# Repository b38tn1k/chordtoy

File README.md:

# chordtoy

not an arpeggiator :-P

A dual channel MIDI chord generator with 'strumming' on one channel

I am not that great at building cases, here are my v1 and v2 prototypes.

[videos are easier than reading](https://www.youtube.com/playlist?list=PLZttbibA79ov0Y0J_pEOQnuLViuv8ho1e)

[how to install arduino midi library](https://github.com/FortySevenEffects/arduino_midi_library)

***built on a tested with MIDI Library version 4.3.1***

I wanted to play chords using the Arturia BeatStep Pro sequencer. This sits in the MIDI chain between the sequencer and the synth and uses the incoming MIDI note to stack a chord.*

## Features

- **Major / Minor Switch**. Major mode has a dominant 7th rather than major 7th chord, I haven't used it much.

- **Key Selector Pot:** Choose the key, other chords are mapped to scale for diatonic chords (I hope/think)

- **Chord Selector Pot:** Starting with the root note, add more notes to create a more complex sound. I tried to group the less complex sounds at low values and the more extreme sounds at high values. So, in Minor mode you can turn up to go from one note to a power chord to a minor chord to a minor 7, 9th, 11th, 13th.. with a couple more variations.

- **Inversion Mode Pot:** at zero the root note is at the bottom. At 100% the root note is at the top of the chord. Variations exist in between.

- **Strum Rate Pot:** When I first made this I just wanted to play simple block chords for techno-y sounding stabs on the DX. By accident I realized that the strummed chord can sound really nice and give some movement to a beat. Rhythms like [Legowelt](https://youtu.be/TGCxBVu1-sE) or [Flying Lotus](https://youtu.be/Pc0OaUQJtd4)... so at one extreme the chord plays all at once. At the other extreme the notes are plucked out one at a time slowly. Yes, like an arpeggiator. but no repeating or syncing cause I have a BeatStep that can keep time and play arpeggios :-)

- a **Legato Switch** changes the way MIDI noteoff messages are sent, allowing the strummed chord to ring out from a trigger or be cut short.

- a **Bypass Switch**, turn off the effect. More useful than turning everything down as in V1.

- a **Second MIDI Channel**. The ```MIDI_STRUM_CHANNEL``` does the 'strumming' chord effect. The ```MIDI_BLOCK_CHORD_CHANNEL``` is used to transmit block chords with the same notes as the Master chord, but with its own unique settings. It works nicely with my (newish) Behringer Crave in arp mode, giving me a 'free time' chord flourish from the DX and accompanying in time Arpeggios from the Crave. If you dont want the second channel stuff just don't let any devices listen on that channel and it should be fine, maybe tie the 'chord size' analog pin to ground :)

- **Second Inversion Mode**: as above but for the ```MIDI_BLOCK_CHORD_CHANNEL```, and with notes shifted 2 octaves cause I like it more.

- **Chord Size**: increase the number of notes in the ```MIDI_BLOCK_CHORD_CHANNEL``` by adding octaves above and below.

## Building

See below for my early prototypes, there is an ***in development*** kicad project included in this repo. Maybe someone good at EE can help? hmu!

Basically, you want to connect MIDI DINs to the Tx and Rx of the Arduino [I used this instructable](https://www.instructables.com/Send-and-Receive-MIDI-with-Arduino/). There are 6 pots, 3 switches and 2 LEDS in the current prototype, you can see the pin assignments in the .ino file.

Version 1 GPIOs per the .ino sketch:

Version 2 is similar with pot and switch IOs listed at top of the .ino file.

Prototype using a Pro Trinket (same pinouts as UNO) before I made it diatonic:

## Almost TODOs, Maybe just ideas

- MIDI CC Control for the various pots and switches
- Does [FortySevenEffect](https://github.com/FortySevenEffects/arduino_midi_library) MIDI library support transport, tempo, etc pass through?

\* Akai and Oberheim used to make boxes that did this sort of thing and this functionality is now built into heaps of DAWs, possible some synths. my Yamaha DX doesn't

Thank you to David Fodel for testing, advice and motivation!

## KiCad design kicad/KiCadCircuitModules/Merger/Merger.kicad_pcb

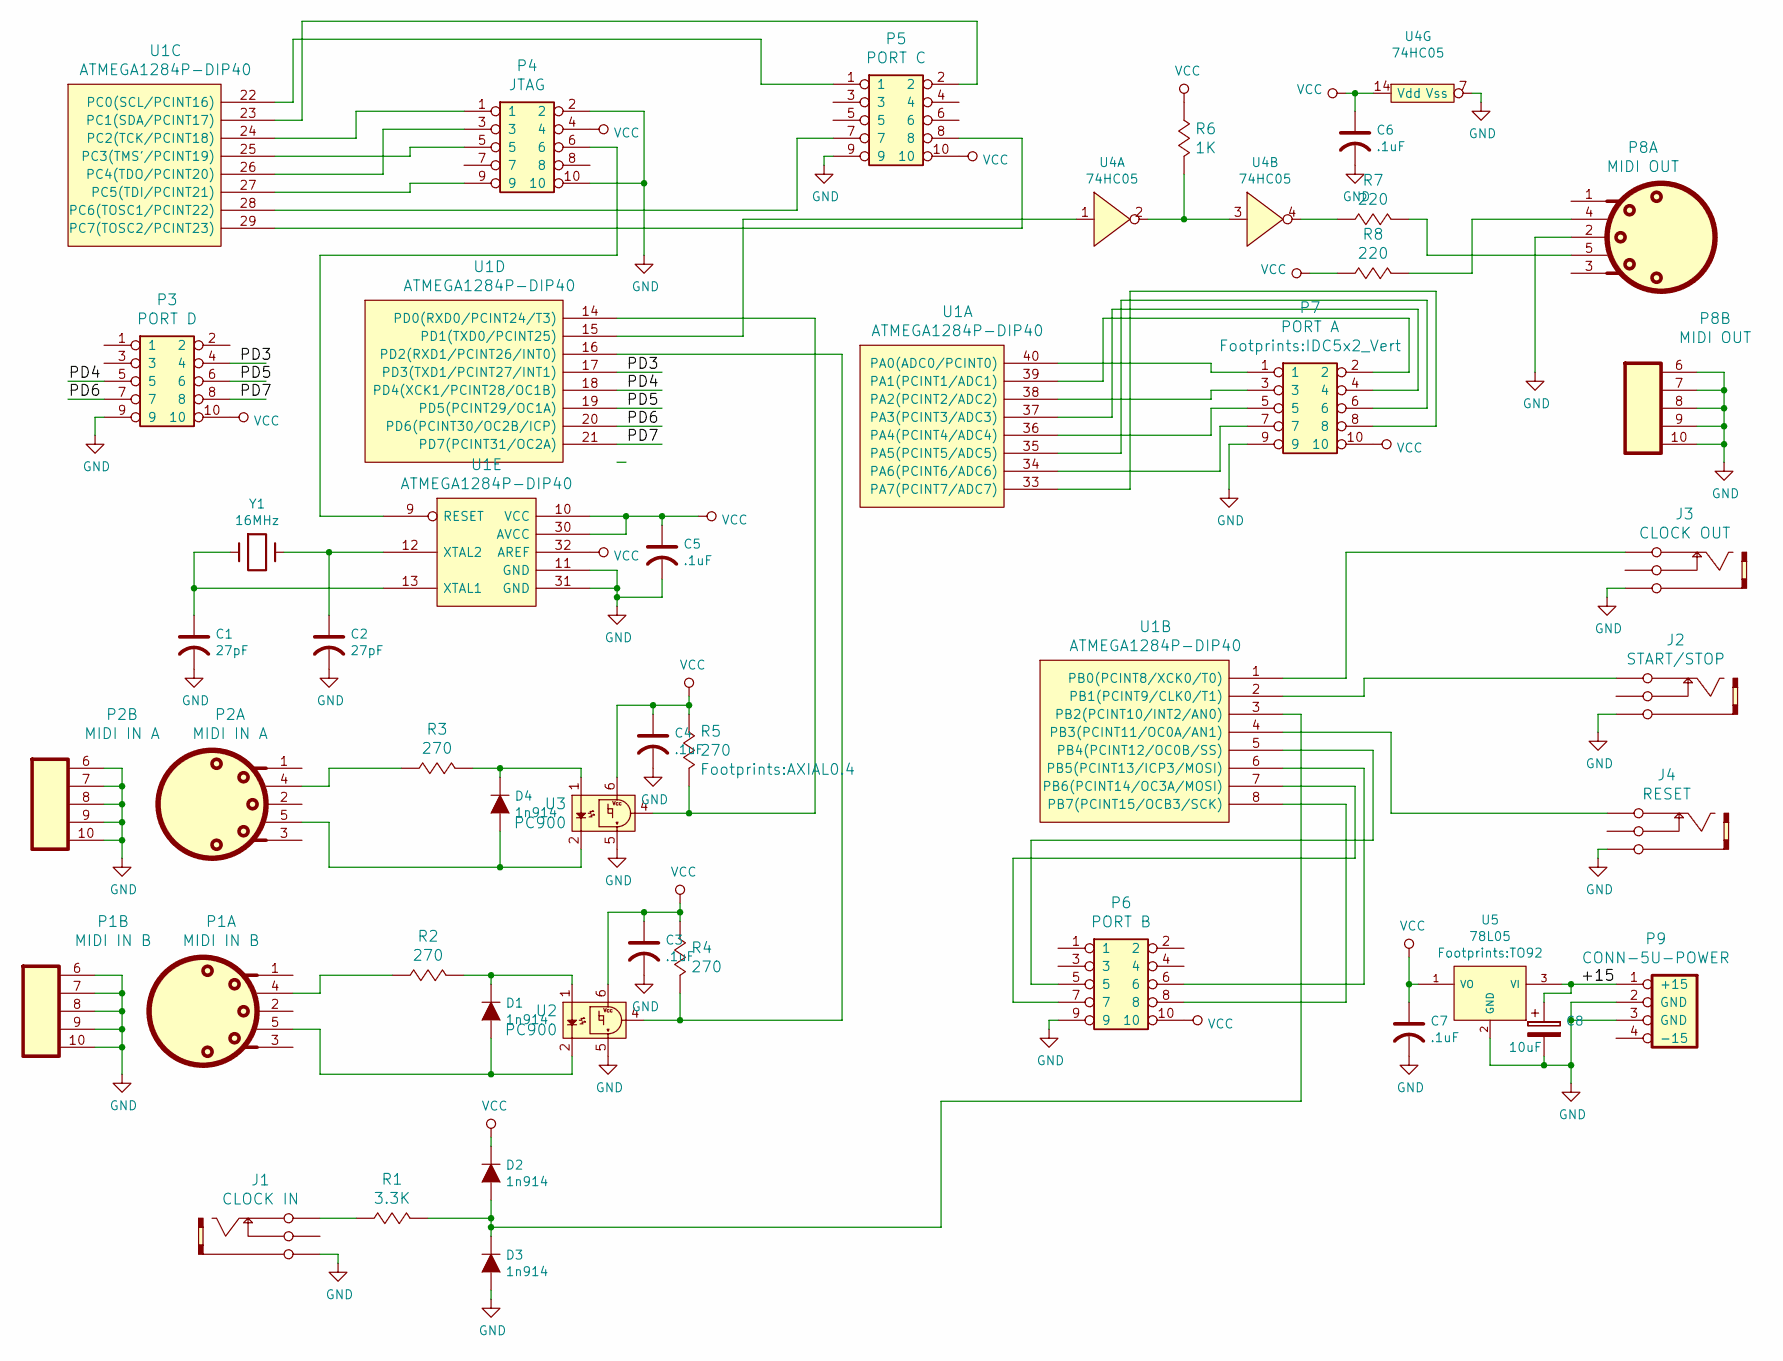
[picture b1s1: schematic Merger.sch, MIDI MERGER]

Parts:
C1, C2: 27pF; CAP-0.1
C3, C4, C5, C6, C7: .1uF; CAP-Bypass-0.3
C8: 10uF; C_Radial_D10_L13_P5
D1, D2, D3, D4: 1n914; DIODE0.4
J1: CLOCK IN; PHONE-SC112A
J2: START/STOP; PHONE-SC112A
J3: CLOCK OUT; PHONE-SC112A
J4: RESET; PHONE-SC112A
P1: MIDI IN B; DIN-5-PIN
P2: MIDI IN A; DIN-5-PIN
P3: PORT D; IDC5x2_Vert
P4: JTAG; IDC5x2_Vert
P5: PORT C; IDC5x2_Vert
P6: PORT B; IDC5x2_Vert
P7: PORT A; IDC5x2_Vert
P8: MIDI OUT; DIN-5-PIN
P9: CONN-5U-POWER; CONN-5U-POWER-RA
R1: 3.3K; AXIAL0.4
R2, R3, R4, R5: 270; AXIAL0.4
R6: 1K; AXIAL0.4
R7, R8: 220; AXIAL0.4
U1: ATMEGA1284P-DIP40; DIP-40.6
U2, U3: PC900; DIP-6.3
U4: 74HC05; DIP-14.3
U5: 78L05; TO92
Y1: 16MHz; XTAL

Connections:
/+15: C8.1, P9.1 (+15), U5.3 (VI)
/PD3: P3.4, U1.17 (PD3(TXD1/PCINT27/INT1))
/PD4: P3.5, U1.18 (PD4(XCK1/PCINT28/OC1B))
/PD5: P3.6, U1.19 (PD5(PCINT29/OC1A))
/PD6: P3.7, U1.20 (PD6(PCINT30/OC2B/ICP))
/PD7: P3.8, U1.21 (PD7(PCINT31/OC2A))
GND: C1.2, C2.2, C3.2, C4.2, C5.2, C6.2, C7.2, C8.2, D3.2 (A), J1.1 (Gnd), J2.1 (Gnd), J3.1 (Gnd), J4.1 (Gnd), P1.6 (Mounting_Pad), P1.7 (Mounting_Pad), P1.8 (Mounting_Pad), P1.9 (Mounting_Pad), P1.10 (Mounting_Pad), P2.6 (Mounting_Pad), P2.7 (Mounting_Pad), P2.8 (Mounting_Pad), P2.9 (Mounting_Pad), P2.10 (Mounting_Pad), P3.9, P4.2, P4.10, P5.9, P6.9, P7.9, P8.2, P8.6 (Mounting_Pad), P8.7 (Mounting_Pad), P8.8 (Mounting_Pad), P8.9 (Mounting_Pad), P8.10 (Mounting_Pad), P9.2 (GND), P9.3 (GND), U1.11 (GND), U1.31 (GND), U2.5 (GND), U3.5 (GND), U4.7 (Vss), U5.2 (GND)
unnamed: C1.1, U1.13 (XTAL1), Y1.1
unnamed: C2.1, U1.12 (XTAL2), Y1.2
unnamed: D1.1 (K), R2.2 (B), U2.1 (A)
unnamed: D1.2 (A), P1.5, U2.2 (C)
unnamed: D2.2 (A), D3.1 (K), R1.2 (B), U1.3 (PB2(PCINT10/INT2/AN0))
unnamed: D4.1 (K), R3.2 (B), U3.1 (A)
unnamed: D4.2 (A), P2.5, U3.2 (C)
unnamed: J1.3 (Tip), R1.1 (A)
unnamed: J2.3 (Tip), U1.2 (PB1(PCINT9/CLK0/T1))
unnamed: J3.3 (Tip), U1.1 (PB0(PCINT8/XCK0/T0))
unnamed: J4.3 (Tip), U1.4 (PB3(PCINT11/OC0A/AN1))
unnamed: P1.4, R2.1 (A)
unnamed: P2.4, R3.1 (A)
unnamed: P4.1, U1.24 (PC2(TCK/PCINT18))
unnamed: P4.3, U1.26 (PC4(TDO/PCINT20))
unnamed: P4.5, U1.25 (PC3(TMS'/PCINT19))
unnamed: P4.6, U1.9 (RESET)
unnamed: P4.9, U1.27 (PC5(TDI/PCINT21))
unnamed: P5.1, U1.22 (PC0(SCL/PCINT16))
unnamed: P5.2, U1.23 (PC1(SDA/PCINT17))
unnamed: P5.7, U1.28 (PC6(TOSC1/PCINT22))
unnamed: P5.8, U1.29 (PC7(TOSC2/PCINT23))
unnamed: P6.5, U1.5 (PB4(PCINT12/OC0B/SS))
unnamed: P6.6, U1.6 (PB5(PCINT13/ICP3/MOSI))
unnamed: P6.7, U1.7 (PB6(PCINT14/OC3A/MOSI))
unnamed: P6.8, U1.8 (PB7(PCINT15/OCB3/SCK))
unnamed: P7.1, U1.40 (PA0(ADC0/PCINT0))
unnamed: P7.2, U1.39 (PA1(PCINT1/ADC1))
unnamed: P7.3, U1.38 (PA2(PCINT2/ADC2))
unnamed: P7.4, U1.37 (PA3(PCINT3/ADC3))
unnamed: P7.5, U1.36 (PA4(PCINT4/ADC4))
unnamed: P7.6, U1.35 (PA5(PCINT5/ADC5))
unnamed: P7.7, U1.34 (PA6(PCINT6/ADC6))
unnamed: P7.8, U1.33 (PA7(PCINT7/ADC7))
unnamed: P8.4, R8.2 (B)
unnamed: P8.5, R7.2 (B)
unnamed: R4.2 (B), U1.16 (PD2(RXD1/PCINT26/INT0)), U2.4 (OUT)
unnamed: R5.2 (B), U1.14 (PD0(RXD0/PCINT24/T3)), U3.4 (OUT)
unnamed: R6.2 (B), U4.2, U4.3
unnamed: R7.1 (A), U4.4
unnamed: U1.15 (PD1(TXD0/PCINT25)), U4.1
VCC: C3.1, C4.1, C5.1, C6.1, C7.1, D2.1 (K), P3.10, P4.4, P5.10, P6.10, P7.10, R4.1 (A), R5.1 (A), R6.1 (A), R8.1 (A), U1.10 (VCC), U1.30 (AVCC), U1.32 (AREF), U2.6 (VCC), U3.6 (VCC), U4.14 (Vdd), U5.1 (VO)

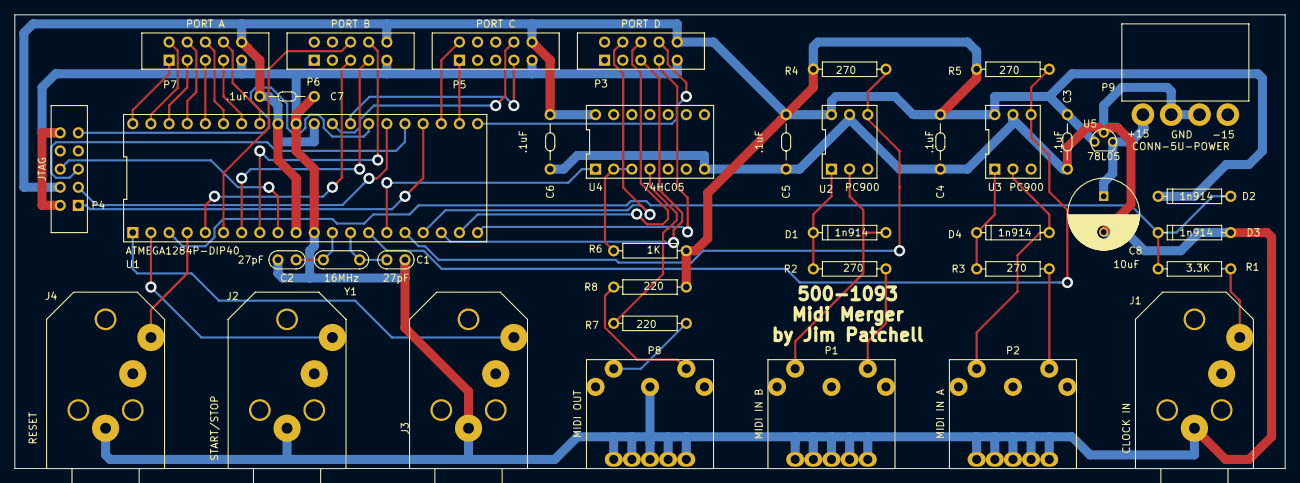
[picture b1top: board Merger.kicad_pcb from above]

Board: 2 copper layers, 177.8 x 63.5 mm, 39 parts (0 on the bottom side), 49 nets.

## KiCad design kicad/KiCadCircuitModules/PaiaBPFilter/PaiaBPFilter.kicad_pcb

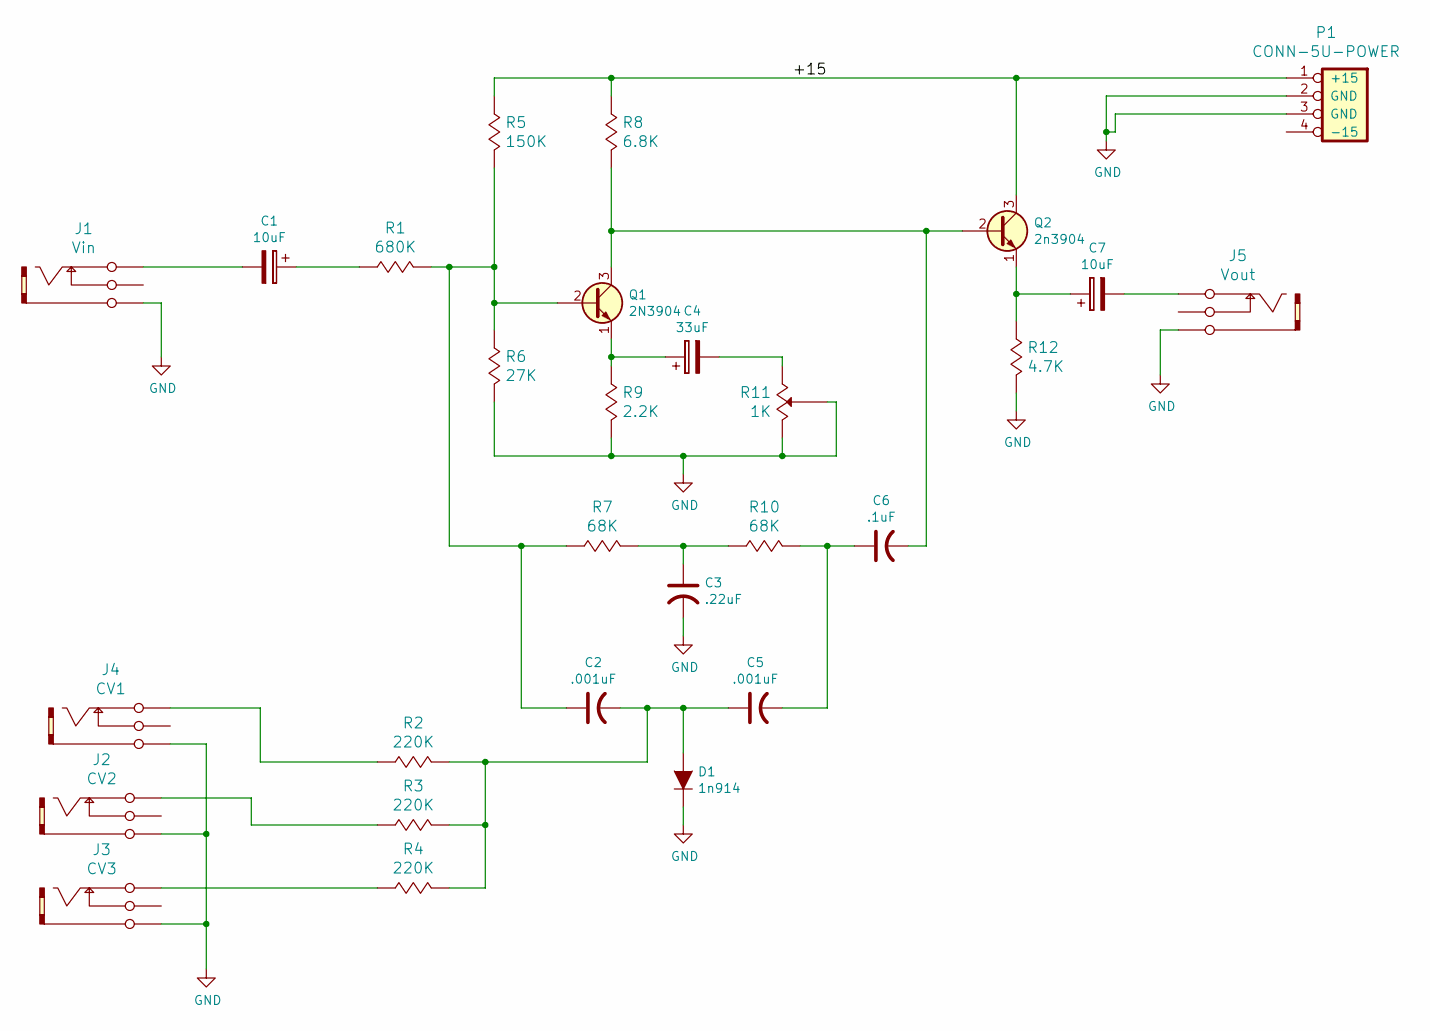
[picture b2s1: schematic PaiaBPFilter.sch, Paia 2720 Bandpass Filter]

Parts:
C1, C7: 10uF; C_Radial_D10_L20_P2.5
C2, C5: .001uF; CAP-GREENIE-0.2
C3: .22uF; CAP-GREENIE-0.2
C4: 33uF; C_Radial_D10_L20_P2.5
C6: .1uF; CAP-GREENIE-0.2
D1: 1n914; DIODE0.4
J1: Vin; PHONE-SC112A
J2: CV2; PHONE-SC112A
J3: CV3; PHONE-SC112A
J4: CV1; PHONE-SC112A
J5: Vout; PHONE-SC112A
P1: CONN-5U-POWER; CONN-5U-POWER-RA
Q1: 2N3904; TO92
Q2: 2n3904; TO92
R1: 680K; AXIAL0.4
R2, R3, R4: 220K; AXIAL0.4
R5: 150K; AXIAL0.4
R6: 27K; AXIAL0.4
R7, R10: 68K; AXIAL0.4
R8: 6.8K; AXIAL0.4
R9: 2.2K; AXIAL0.4
R11: 1K; POT-Alpha-24mm-RA
R12: 4.7K; AXIAL0.4

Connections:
/+15: P1.1 (+15), Q2.3 (C), R5.1 (A), R8.1 (A)
GND: C3.2, D1.1 (K), J1.1 (Gnd), J2.1 (Gnd), J3.1 (Gnd), J4.1 (Gnd), J5.1 (Gnd), P1.2 (GND), P1.3 (GND), R6.2 (B), R9.2 (B), R11.2 (Wiper), R11.3 (B), R12.2 (B)
unnamed: C1.1, R1.1 (A)
unnamed: C1.2, J1.3 (Tip)
unnamed: C2.1, Q1.2 (B), R1.2 (B), R5.2 (B), R6.1 (A), R7.1 (A)
unnamed: C2.2, C5.1, D1.2 (A), R2.2 (B), R3.2 (B), R4.2 (B)
unnamed: C3.1, R7.2 (B), R10.1 (A)
unnamed: C4.1, Q1.1 (E), R9.1 (A)
unnamed: C4.2, R11.1 (A)
unnamed: C5.2, C6.1, R10.2 (B)
unnamed: C6.2, Q1.3 (C), Q2.2 (B), R8.2 (B)
unnamed: C7.1, Q2.1 (E), R12.1 (A)
unnamed: C7.2, J5.3 (Tip)
unnamed: J2.3 (Tip), R3.1 (A)
unnamed: J3.3 (Tip), R4.1 (A)
unnamed: J4.3 (Tip), R2.1 (A)

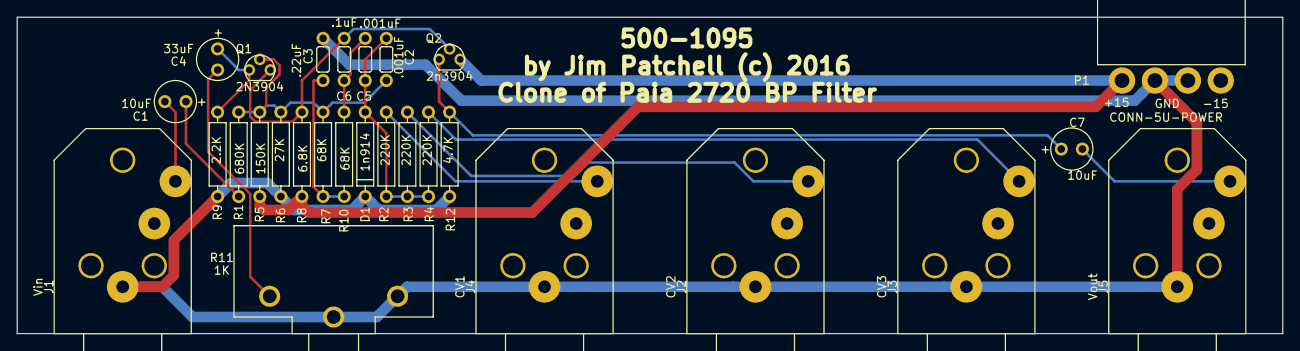
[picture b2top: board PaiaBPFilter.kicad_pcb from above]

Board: 2 copper layers, 152.4 x 38.1 mm, 28 parts (0 on the bottom side), 16 nets.

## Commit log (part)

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2019-10-23 fixes
2019-10-23 suprisingly musical
2019-10-24 Inversion Pot, other things
2019-10-24 fritzing
2019-10-24 readme stuff
2019-10-24 smaller cat image (highly important)
2019-10-26 first run, wanna switch back fro a sec
2019-10-26 cleaning
2019-10-26 testing, bug searching
2019-10-28 memory crash i think :-/
2019-10-28 prereset1
2019-10-28 diatonic chords
    still have to make the diminished chord shapes
2019-10-28 added diminished mapping
2020-05-29 v2 for 2x MIDI things
2020-05-30 Legato sounding really nice, something weird with update the arp/pad channel when things change
2020-05-30 All features working
2020-05-30 added Note Off message for bypass switching channel 2, also a photo without a cat :-(
2020-05-30 Create LICENSE
2020-05-31 sound testing stuff
2021-04-13 Update README.md
    Making adjustments to work with multiple individual MIDI input channels - one input channel for Pad/Arp function, and another input channel for the Strum routines. Also need to clean-up some of the N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
2021-05-31 more intentional seperation of channels, further dev on NoteOff required
2021-05-31 basic note off behavior
2021-05-31 reinstate bypass, hopefully
2021-05-31 duplicate note fix
2021-05-31 some channel seperation
2021-06-02 logic that seperates Strum and Block Chord channels, hopefully decent NoteOff behavior
2021-07-06 v2, trying to seperate Strums and blocks
2021-07-06 mirrored logic to NoteOff
2021-11-15 duration
2021-11-22 Mega code

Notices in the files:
kicad/KiCadCircuitModules/PaiaBPFilter/PaiaBPFilter.kicad_pcb:
by Jim Patchell (c) 2016
